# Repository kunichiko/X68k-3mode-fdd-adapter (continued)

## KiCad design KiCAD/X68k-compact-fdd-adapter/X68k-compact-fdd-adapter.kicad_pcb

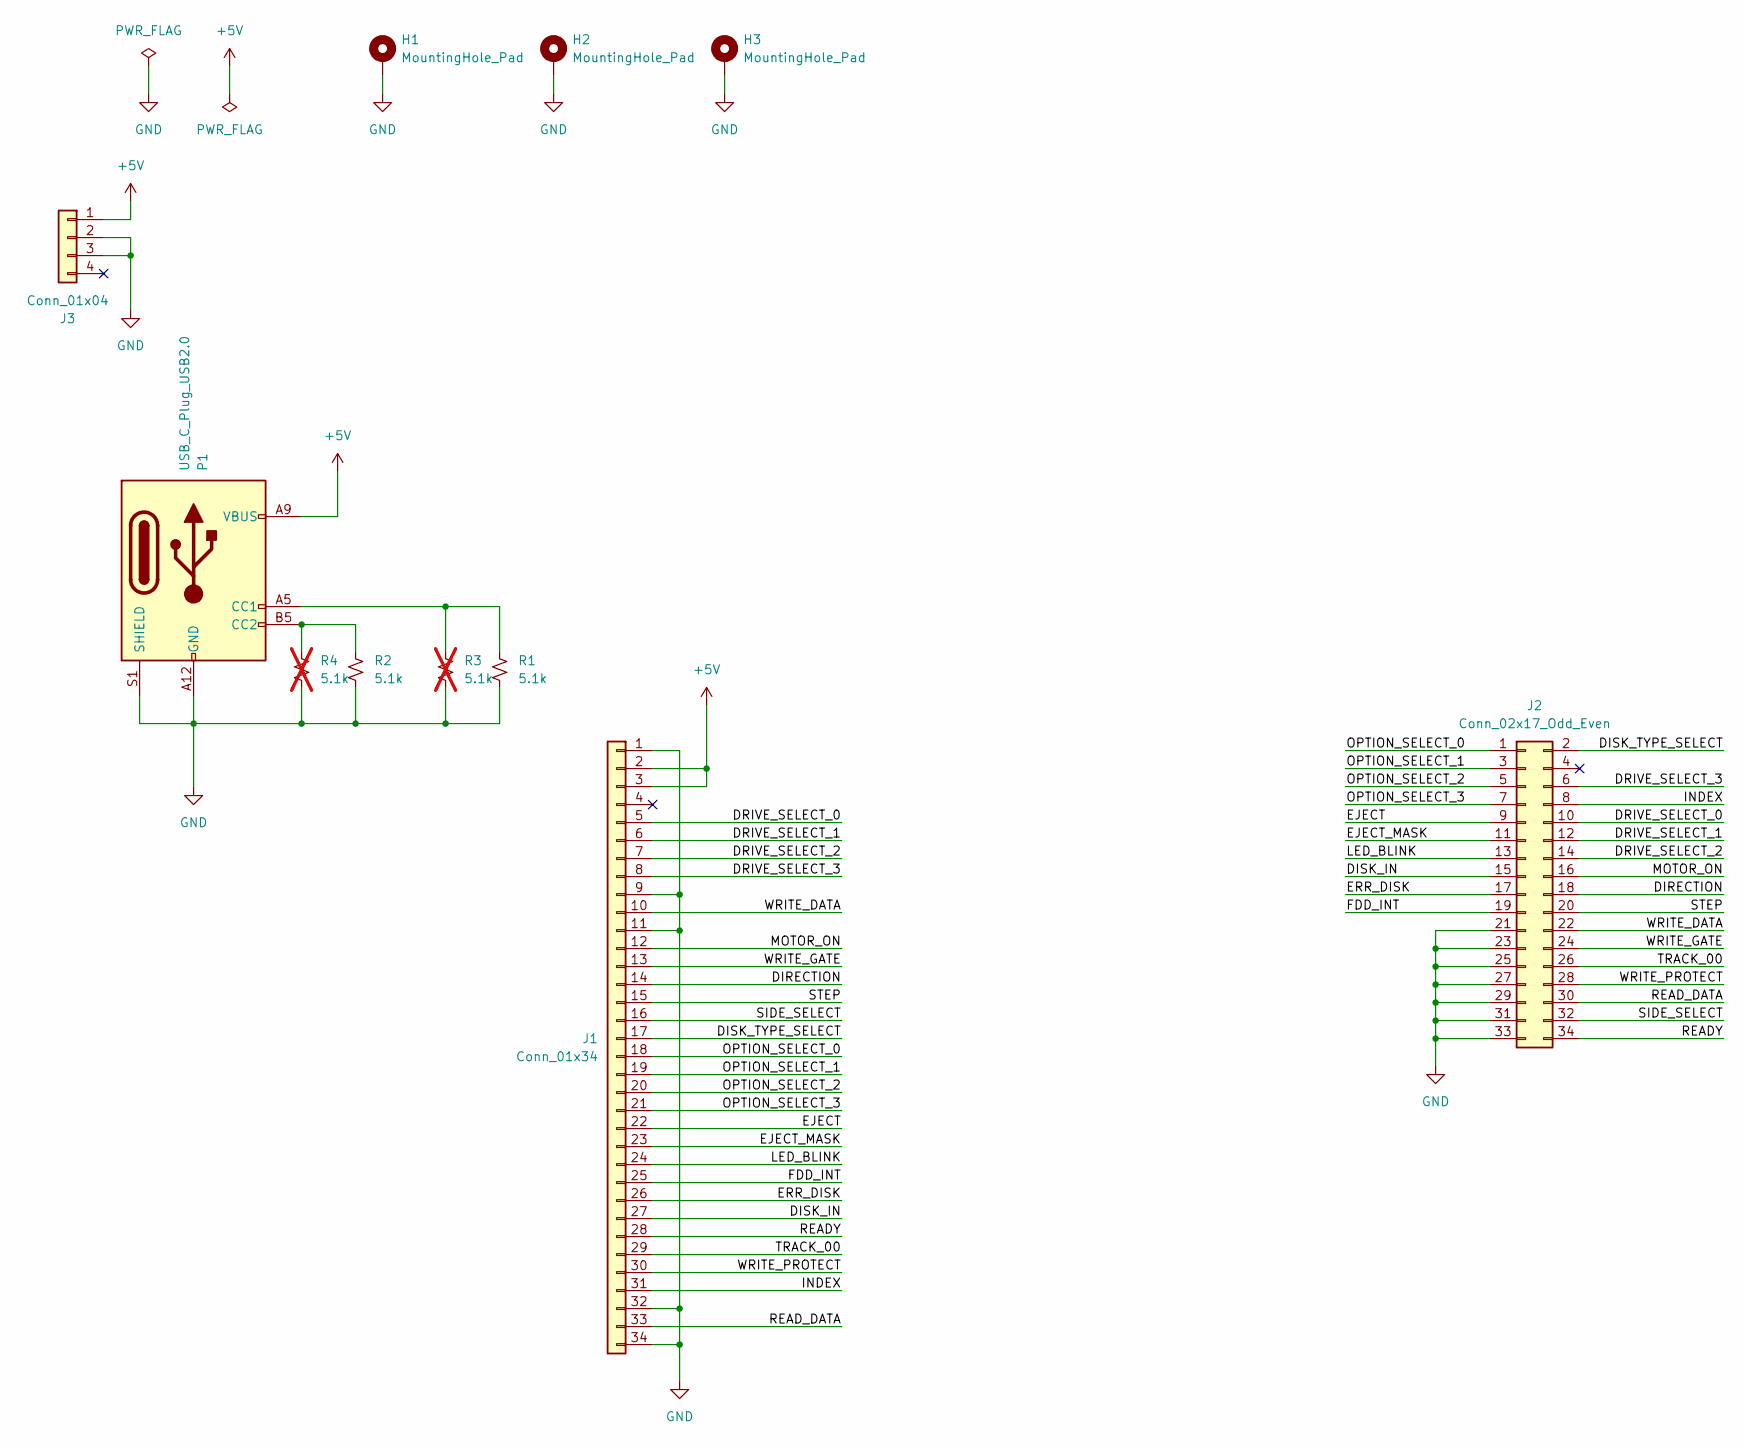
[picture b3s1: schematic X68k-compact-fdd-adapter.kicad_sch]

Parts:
H1, H2, H3: MountingHole_Pad; MountingHole_2.7mm_M2.5_Pad
J1: Conn_01x34; JST-34FE-FCC
J2: Conn_02x17_Odd_Even; PinHeader_2x17_P2.54mm_Horizontal_Mirror; LCSC C725929
J3: Conn_01x04; TE_AMP_171826-4; LCSC C590635
P1: USB_C_Plug_USB2.0; USB_C_Receptacle_GCT_USB4125-xx-x-0190_6P_TopMnt_Horizontal; LCSC C168701
R1, R2: 5.1k; R_0603_1608Metric
R3, R4: 5.1k; R_Axial_DIN0204_L3.6mm_D1.6mm_P5.08mm_Horizontal; not fitted

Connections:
+5V: J1.2, J1.3, J3.1, P1.A9 (VBUS), P1.B9 (VBUS)
/DIRECTION: J1.14, J2.18
/DISK_IN: J1.27, J2.15
/DISK_TYPE_SELECT: J1.17, J2.2
/DRIVE_SELECT_0: J1.5, J2.10
/DRIVE_SELECT_1: J1.6, J2.12
/DRIVE_SELECT_2: J1.7, J2.14
/DRIVE_SELECT_3: J1.8, J2.6
/EJECT: J1.22, J2.9
/EJECT_MASK: J1.23, J2.11
/ERR_DISK: J1.26, J2.17
/FDD_INT: J1.25, J2.19
/INDEX: J1.31, J2.8
/LED_BLINK: J1.24, J2.13
/MOTOR_ON: J1.12, J2.16
/OPTION_SELECT_0: J1.18, J2.1
/OPTION_SELECT_1: J1.19, J2.3
/OPTION_SELECT_2: J1.20, J2.5
/OPTION_SELECT_3: J1.21, J2.7
/READY: J1.28, J2.34
/READ_DATA: J1.33, J2.30
/SIDE_SELECT: J1.16, J2.32
/STEP: J1.15, J2.20
/TRACK_00: J1.29, J2.26
/WRITE_DATA: J1.10, J2.22
/WRITE_GATE: J1.13, J2.24
/WRITE_PROTECT: J1.30, J2.28
GND: H1.1, H2.1, H3.1, J1.1, J1.9, J1.11, J1.32, J1.34, J2.21, J2.23, J2.25, J2.27, J2.29, J2.31, J2.33, J3.2, J3.3, P1.A12 (GND), P1.B12 (GND), P1.S1 (SHIELD), R1.1, R2.2, R3.1, R4.1
unnamed: P1.A5 (CC1), R1.2, R3.2
unnamed: P1.B5 (CC2), R2.1, R4.2

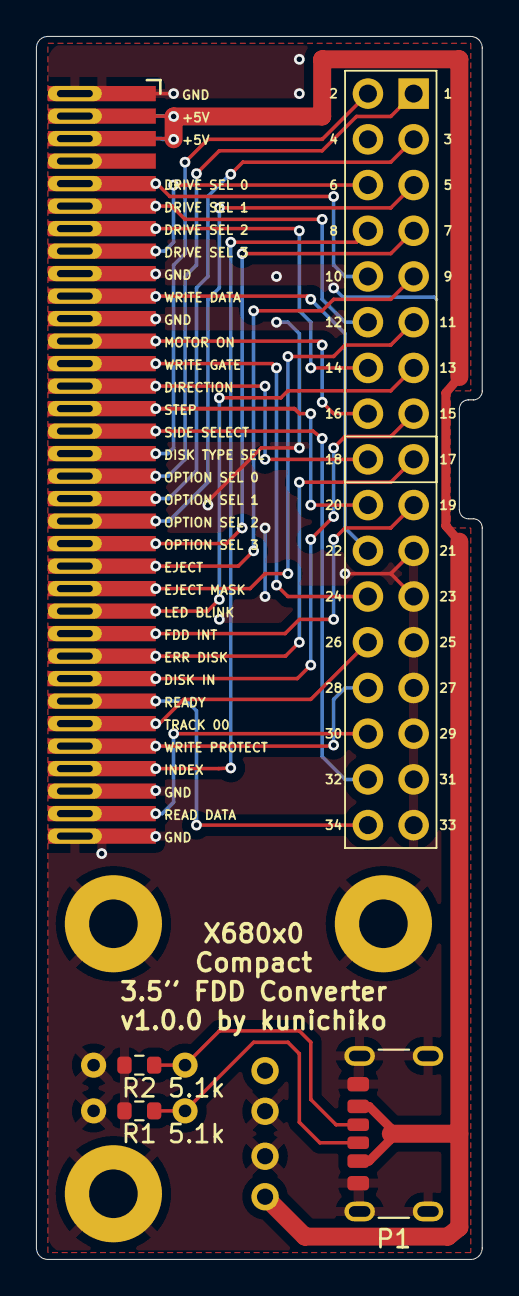
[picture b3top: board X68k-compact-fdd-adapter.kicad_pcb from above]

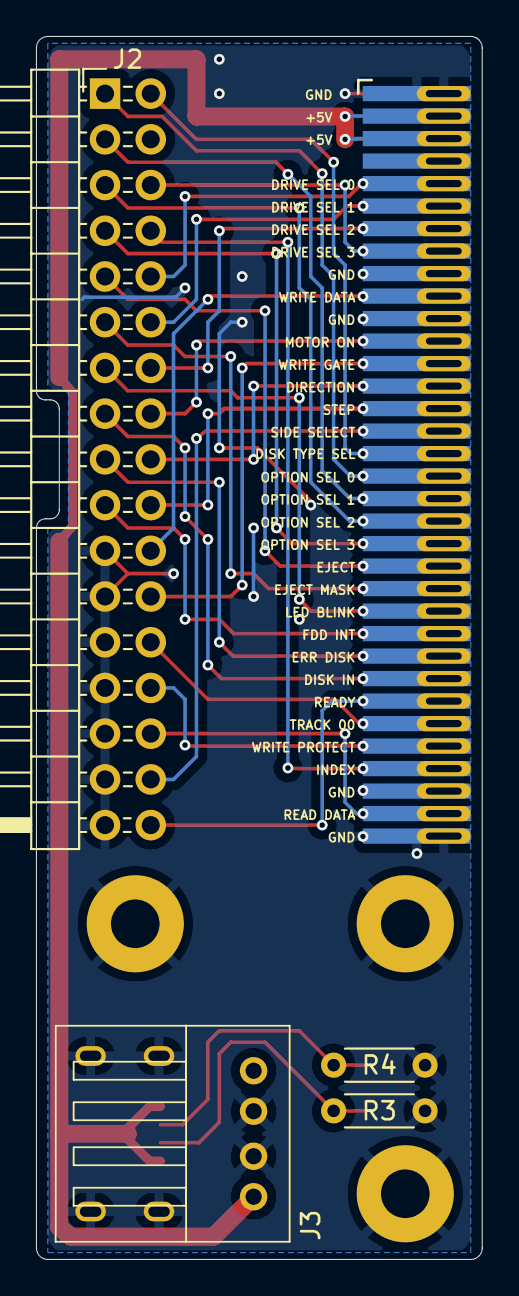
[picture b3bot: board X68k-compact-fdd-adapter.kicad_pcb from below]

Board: 2 copper layers, 24.8 x 67.9 mm, 11 parts (4 on the bottom side), 30 nets.

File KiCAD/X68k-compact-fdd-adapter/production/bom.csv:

Designator,Footprint,Quantity,Value,LCSC Part #
J1,JST-34FE-FFC,1,Conn_01x34,
J2,PinHeader_2x17_P2.54mm_Horizontal_Mirror,1,Conn_02x17_Odd_Even,C725929
J3,TE_AMP_171826-4,1,Conn_01x04,C590635
P1,USB_C_Receptacle_GCT_USB4125-xx-x-0190_6P_TopMnt_Horizontal,1,USB_C_Plug_USB2.0,C168701
"R1, R2",0603,2,5.1k,

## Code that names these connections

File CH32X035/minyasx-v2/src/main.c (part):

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    RCC->APB1PCENR |= RCC_TIM2EN | RCC_TIM3EN;
    RCC->APB2PCENR = RCC_IOPDEN | RCC_IOPCEN | RCC_IOPBEN | RCC_IOPAEN | RCC_TIM1EN | RCC_SPI1EN | RCC_AFIOEN;

    // SPIをデフォルトのPA6,7(MISO,MOSI)から、PC6,7(MISO_3,MOSI_3)に変更するために、Remap Register 1 でリマップする
    AFIO->PCFR1 &= ~(AFIO_PCFR1_SPI1_REMAP);                           // SPI1 remap をクリア
    AFIO->PCFR1 |= AFIO_PCFR1_SPI1_REMAP_1 | AFIO_PCFR1_SPI1_REMAP_0;  // SPI1 remap を 3 (0b11) にセット

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    RCC->APB1PRSTR &= ~RCC_APB1Periph_TIM3;

    // GPIOA
    // PA0 : DRIVE_SELECT_A (入力: Low=inactive, High=active, Pull-Up)
    // PA1 : DRIVE_SELECT_B (入力: Low=inactive, High=active, Pull-Up)
    // PA2 : OPTION_SELECT_A (入力: Low=inactive, High=active, Pull-Up)
    // PA3 : OPTION_SELECT_B (入力: Low=inactive, High=active, Pull-Up)
    // PA4 : OPTION_SELECT_B_PAIR (入力: Low=inactive, High=active, Pull-Up)
    // PA5 : DISK_TYPE_SELECT (入力: Pull-Up, 未使用)
    // PA6 : INDEX_DOSV (入力: INDEX信号, Pull-Up)
    // PA7 : Buzzer (出力: PWM)
    // PA8 : WRITE_GATE_MCU (出力: 将来拡張用)
    // PA9 : WRITE_DATA_MCU (出力: 将来拡張用)
    // PA10: I2C_SCL (I2Cクロック)
    // PA11: I2C_SDA (I2Cデータ)
    // PA12: MOTOR_ON (入力: Low=ON, High=OFF, Pull-Up)
    // PA13: EJECT_n (入力: Low=イジェクト, Pull-Up)
    // PA14: EJECT_MASK_n (入力: Low=イジェクト禁止, Pull-Up)
    // PA15: LED_BLINK_n (入力: Low=点灯, Pull-Up)
    // PA16: X68_PWR (入力: Low=電源ON要求, Pull-Up)
    // PA17: +12V_EXT_DET (High=外部+12V電源接続, Pull-Up)
    // PA18: +5V_EN (Low=Enable, High=Disable)
    // PA19: +12V_EN (Low=Enable, High=Disable)
    // PA20: +12V_EXT_EN (Low=Enable, High=Disable))
    // PA22: DIPSW_DS0 (入力: Pull-Up)
    // PA23: DIPSW_DS1 (入力: Pull-Up)

    // PA0: DRIVE_SELECT_A input
    GPIOA->CFGLR &= ~(0xf << (4 * 0));
    GPIOA->CFGLR |= (GPIO_Speed_In | GPIO_CNF_IN_PUPD) << (4 * 0);
    GPIOA->BSHR = (1 << 0);  // Pull-Up
    // PA1: DRIVE_SELECT_B input
    GPIOA->CFGLR &= ~(0xf << (4 * 1));
    GPIOA->CFGLR |= (GPIO_Speed_In | GPIO_CNF_IN_PUPD) << (4 * 1);
    GPIOA->BSHR = (1 << 1);  // Pull-Up
    // PA2: OPTION_SELECT_A input
    GPIOA->CFGLR &= ~(0xf << (4 * 2));
    GPIOA->CFGLR |= (GPIO_Speed_In | GPIO_CNF_IN_PUPD) << (4 * 2);
    GPIOA->BSHR = (1 << 2);  // Pull-Up
    // PA3: OPTION_SELECT_B input
    GPIOA->CFGLR &= ~(0xf << (4 * 3));
    GPIOA->CFGLR |= (GPIO_Speed_In | GPIO_CNF_IN_PUPD) << (4 * 3);
    GPIOA->BSHR = (1 << 3);  // Pull-Up
    // PA4: OPTION_SELECT_B_PAIR input
    GPIOA->CFGLR &= ~(0xf << (4 * 4));
    GPIOA->CFGLR |= (GPIO_Speed_In | GPIO_CNF_IN_PUPD) << (4 * 4);
    GPIOA->BSHR = (1 << 4);  // Pull-Up
    // PA5: DISK_TYPE_SELECT input
    GPIOA->CFGLR &= ~(0xf << (4 * 5));
    GPIOA->CFGLR |= (GPIO_Speed_In | GPIO_CNF_IN_PUPD) << (4 * 5);
    GPIOA->BSHR = (1 << 5);  // Pull-Up
    // PA6: INDEX_DOSV input
    GPIOA->CFGLR &= ~(0xf << (4 * 6));
    GPIOA->CFGLR |= (GPIO_Speed_In | GPIO_CNF_IN_PUPD) << (4 * 6);
    GPIOA->BSHR = (1 << 6);  // Pull-Up
    // PA7 : Buzzer output. TIM3_CH2 (PWM出力)
    GPIOA->CFGLR &= ~(0xf << (4 * 7));
    // GPIOA->CFGLR |= (GPIO_Speed_50MHz | GPIO_CNF_OUT_PP_AF) << (4 * 7);
    GPIOA->CFGLR |= (GPIO_Speed_50MHz | GPIO_CNF_OUT_PP) << (4 * 7);
    //  GPIOA->CFGLR |= (GPIO_Speed_In | GPIO_CNF_IN_PUPD) << (4 * 7);
    GPIOA->BCR = (1 << 7);  // Low出力にする
    // GPIOA->BSHR = (1 << 7);  // High出力にする (Buzzer OFF)
    // PA8: WRITE_GATE_MCU output
    GPIOA->CFGHR &= ~(0xf << (4 * (8 - 8)));
    GPIOA->CFGHR |= (GPIO_Speed_50MHz | GPIO_CNF_OUT_PP) << (4 * (8 - 8));
    GPIOA->BCR = (1 << 8);  // 0を出力 (この先にいるFETをOFFにする)
    // PA9: WRITE_DATA_MCU output
    GPIOA->CFGHR &= ~(0xf << (4 * (9 - 8)));
    GPIOA->CFGHR |= (GPIO_Speed_50MHz | GPIO_CNF_OUT_PP) << (4 * (9 - 8));
    GPIOA->BCR = (1 << 9);  // 0を出力 (この先にいるFETをOFFにする)
    // PA10: I2C_SCL
    // PA11: I2C_SDA
    // PA12: MOTOR_ON input
    GPIOA->CFGHR &= ~(0xf << (4 * (12 - 8)));
    GPIOA->CFGHR |= (GPIO_Speed_In | GPIO_CNF_IN_PUPD) << (4 * (12 - 8));
    GPIOA->BSHR = (1 << 12);  // Pull-Up
    // PA13: EJECT_n input
    GPIOA->CFGHR &= ~(0xf << (4 * (13 - 8)));
    GPIOA->CFGHR |= (GPIO_Speed_In | GPIO_CNF_IN_PUPD) << (4 * (13 - 8));
    GPIOA->BSHR = (1 << 13);  // Pull-Up
    // PA14: EJECT_MASK_n input
    GPIOA->CFGHR &= ~(0xf << (4 * (14 - 8)));
    GPIOA->CFGHR |= (GPIO_Speed_In | GPIO_CNF_IN_PUPD) << (4 * (14 - 8));
    GPIOA->BSHR = (1 << 14);  // Pull-Up
    // PA15: LED_BLINK_n input
    GPIOA->CFGHR &= ~(0xf << (4 * (15 - 8)));
    GPIOA->CFGHR |= (GPIO_Speed_In | GPIO_CNF_IN_PUPD) << (4 * (15 - 8));
    GPIOA->BSHR = (1 << 15);  // Pull-Up
    // PA16: X68_PWR input
    GPIOA->CFGXR &= ~(0xf << (4 * (16 - 16)));
    GPIOA->CFGXR |= (GPIO_Speed_In | GPIO_CNF_IN_PUPD) << (4 * (16 - 16));
    GPIOA->BSXR = (1 << (16 - 16));  // Pull-Up
    // PA17: +12V_EXT_DET input
    GPIOA->CFGXR &= ~(0xf << (4 * (17 - 16)));
    GPIOA->CFGXR |= (GPIO_Speed_In | GPIO_CNF_IN_PUPD) << (4 * (17 - 16));
    GPIOA->BSXR = (1 << (17 - 16));  // Pull-Up
    // PA18: +5V_EN output
    GPIOA->CFGXR &= ~(0xf << (4 * (18 - 16)));
    GPIOA->CFGXR |= (GPIO_Speed_50MHz | GPIO_CNF_OUT_PP) << (4 * (18 - 16));
    GPIOA->BCR = (1 << (18));  // Disable (+5V_EN=Low)
    // GPIOA->BSXR = (1 << (18 - 16)); // Enable (+5V_EN=High)
    // PA19: +12V_EN output
    GPIOA->CFGXR &= ~(0xf << (4 * (19 - 16)));
    GPIOA->CFGXR |= (GPIO_Speed_50MHz | GPIO_CNF_OUT_PP) << (4 * (19 - 16));
    GPIOA->BCR = (1 << (19));  // Disable (+12V_EN=Low)
    // GPIOA->BSXR = (1 << (19 - 16)); // Enable (+12V_EN=High)
    //  PA20: +12V_EXT_EN output
    GPIOA->CFGXR &= ~(0xf << (4 * (20 - 16)));
    GPIOA->CFGXR |= (GPIO_Speed_50MHz | GPIO_CNF_OUT_PP) << (4 * (20 - 16));
    GPIOA->BCR = (1 << (20));  // Disable (+12V_EXT_EN=Low)
    // GPIOA->BSXR = (1 << (20 - 16)); // Enable (+12V_EXT_EN=High)

    // PA22: DIPSW_DS0 input
    GPIOA->CFGXR &= ~(0xf << (4 * (22 - 16)));
    GPIOA->CFGXR |= (GPIO_Speed_In | GPIO_CNF_IN_PUPD) << (4 * (22 - 16));
    GPIOA->BSXR = (1 << (22 - 16));  // Pull-Up
    // PA23: DIPSW_DS1 input
    GPIOA->CFGXR &= ~(0xf << (4 * (23 - 16)));
    GPIOA->CFGXR |= (GPIO_Speed_In | GPIO_CNF_IN_PUPD) << (4 * (23 - 16));
    GPIOA->BSXR = (1 << (23 - 16));  // Pull-Up

    // GPIOB
    // PB0 : MODE_SELECT_GP (入力: Low=360RPM, High=300RPM, 逆のものもあるらしい)
    // PB1 : IN_USE_MCU (出力: Low=アクティブ, High=非アクティブ)
    // PB2 : DRIVE_SEL_DOSV_A (未使用, High-Z)
    // PB3 : DRIVE_SEL_DOSV_B (未使用, High-Z)
    // PB4 : DISK_CHANGE_DOSV (入力: Low=ディスクチェンジ, Pull-Up)
    // PB5 : (未使用)
    // PB6 : LOCK_REQ (出力: Low=要求, High=非要求)
    // PB7 : LOCK_ACK (入力: High=アクティブ, Pull-Down)
    // PB8 : WRITE_GATE_GP (入力: フロッピーディスクの書き込み許可信号)
    // PB9 : READ_DATA_DOSV (入力: フロッピーディスクの読み出しデータ)
    // PB10: WRITE_DATA_GP (入力: フロッピーディスクの書き込みデータ)
    // PB11: TRACK0_DOSV (入力: Low=トラック0, Pull-Up)
    // PB12: READY_MCU_A (出力: Low=準備完了, High=準備完了でない)
    // PB13: READY_MCU_B (出力: Low=準備完了

    // PB0: MODE_SELECT_GP input
    GPIOB->CFGLR &= ~(0xf << (4 * 0));
    GPIOB->CFGLR |= (GPIO_Speed_In | GPIO_CNF_IN_FLOATING) << (4 * 0);
    // PB1: IN_USE_MCU output
    GPIOB->CFGLR &= ~(0xf << (4 * 1));
    GPIOB->CFGLR |= (GPIO_Speed_50MHz | GPIO_CNF_OUT_PP) << (4 * 1);
    GPIOB->BCR = (1 << 1);
    // PB2: DRIVE_SELECT_DOSV_A output (未使用)
    GPIOB->CFGLR &= ~(0xf << (4 * 2));
    GPIOB->CFGLR |= (GPIO_Speed_In | GPIO_CNF_IN_FLOATING) << (4 * 2);
    // PB3: DRIVE_SELECT_DOSV_B output (未使用)
    GPIOB->CFGLR &= ~(0xf << (4 * 3));
    GPIOB->CFGLR |= (GPIO_Speed_In | GPIO_CNF_IN_FLOATING) << (4 * 3);
    // PB4: DISK_CHANGE_DOSV input
    GPIOB->CFGLR &= ~(0xf << (4 * 4));
    GPIOB->CFGLR |= (GPIO_Speed_In | GPIO_CNF_IN_PUPD) << (4 * 4);
    GPIOB->BCR = (1 << 4);
    // PB5: (未使用)
    GPIOB->CFGLR &= ~(0xf << (4 * 5));
    GPIOB->CFGLR |= (GPIO_Speed_In | GPIO_CNF_IN_FLOATING) << (4 * 5);
    // PB6: LOCK_REQ output
    GPIOB->CFGLR &= ~(0xf << (4 * 6));
    GPIOB->CFGLR |= (GPIO_Speed_50MHz | GPIO_CNF_OUT_PP) << (4 * 6);
    GPIOB->BCR = (0 << 6);
    // PB7: LOCK_ACK input
    GPIOB->CFGLR &= ~(0xf << (4 * 7));
    GPIOB->CFGLR |= (GPIO_Speed_In | GPIO_CNF_IN_PUPD) << (4 * 7);
    GPIOB->BCR = (1 << 7);  // Pull-Up
    // PB8: WRITE_GATE_GP input
    GPIOB->CFGHR &= ~(0xf << (4 * (8 - 8)));
    GPIOB->CFGHR |= (GPIO_Speed_In | GPIO_CNF_IN_FLOATING) << (4 * (8 - 8));
    // GPIOB->BSHR = (1 << 8);
    //  PB9: READ_DATA_DOSV input
    GPIOB->CFGHR &= ~(0xf << (4 * (9 - 8)));
    GPIOB->CFGHR |= (GPIO_Speed_In | GPIO_CNF_IN_PUPD) << (4 * (9 - 8));
    GPIOB->BSHR = (1 << 9);  // Pull-Up
    // PB10: WRITE_DATA_DOSV input
    GPIOB->CFGHR &= ~(0xf << (4 * (10 - 8)));
    GPIOB->CFGHR |= (GPIO_Speed_In | GPIO_CNF_IN_FLOATING) << (4 * (10 - 8));
    // GPIOB->BSHR = (1 << 10);  // Pull-Up
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    GPIOB->CFGHR &= ~(0xf << (4 * (11 - 8)));
    GPIOB->CFGHR |= (GPIO_Speed_In | GPIO_CNF_IN_PUPD) << (4 * (11 - 8));
    GPIOB->BSHR = (1 << 11);  // Pull-Up
    // PB12: READY_MCU_A output
    GPIOB->CFGHR &= ~(0xf << (4 * (12 - 8)));
    GPIOB->CFGHR |= (GPIO_Speed_50MHz | GPIO_CNF_OUT_PP) << (4 * (12 - 8));
    GPIOB->BSHR = (1 << 12);
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
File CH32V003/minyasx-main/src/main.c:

#include "main.h"

#include <stdarg.h>
#include <stdio.h>

#include "ch32v003_GPIO_branchless.h"
#include "ch32v003fun.h"

#include <ssd1306_txt.h>        // OLED text functions

#include "port_polling.h"

#define WS2812BSIMPLE_IMPLEMENTATION
#include "ws2812b_simple.h"

#define MAIN_LOOP_INTERVAL 100  // 100msごとにメインループを回す

void update_fdd_led();

/**
 * @brief 設定ピンによって、MODE_SELECTの論理を反転するかどうかのフラグ
 *
 */
bool mode_select_invert = 0;

int main() {
    SystemInit();

    Delay_Ms(100);
  
    // Setup OLED
    OLED_init();
    OLED_clear();
    OLED_printf("Minyax-X");

    debugprint("UP\n");

    // 使用するペリフェラルを有効にする
    // IOPDEN = Port D clock enable
    // IOPCEN = Port C clock enable
    // IOPAEN = Port A clock enable
    // TIM1 = Timer 1 module clock enable
    // AFIO = Alternate Function I/O module clock enable
    RCC->APB2PCENR = RCC_IOPDEN | RCC_IOPCEN | RCC_IOPAEN | RCC_TIM1EN | RCC_AFIOEN;

    // リセットレジスタのTIM1RSTをセットしてからクリアすると、
    // タイマー1がリセットされる
    RCC->APB2PRSTR = RCC_TIM1RST;
    RCC->APB2PRSTR = 0;

    //
    // GPIOの設定
    //

    // GPIO A
    // A1: READY,                   Output, Push-Pull
    // A2: BUZZER,                  Output, Push-Pull
    GPIOA->CFGLR &= ~(0xf << (4 * 1));
    GPIOA->CFGLR |= (GPIO_Speed_50MHz | GPIO_CNF_OUT_PP) << (4 * 1);
    GPIOA->CFGLR &= ~(0xf << (4 * 2));
    GPIOA->CFGLR |= (GPIO_Speed_50MHz | GPIO_CNF_OUT_PP) << (4 * 2);

    // GPIO C
    // C0: LED_DATA, Output, push-pull
    //     C0にはスイッチがついていて起動時にHighかLowかでMODE_SELECTの論理を決める
    // C1: I2C SDA
    // C2: I2C SCL
    // C3: FDD INDEX,               Input, pull-up
    // C4: FDD MOTOR_ON,            Input, pull-up
    // C5: FDD DRIVE_SELECT,        Input, pull-up
    // C6: FDD OPTION_SELECT_PAIR,  Input, pull-up
    // C7: FDD OPTION_SELECT,       Input, pull-up

    GPIOC->CFGLR &= ~(0xf << (4 * 0));
    GPIOC->CFGLR |= (GPIO_Speed_In | GPIO_CNF_IN_PUPD) << (4 * 0);
    GPIOC->BSHR = GPIO_Pin_0;  // プルアップを有効にする
    if ((GPIOC->INDR & GPIO_Pin_0) == 0) {
        mode_select_invert = 1;
    } else {
        mode_select_invert = 0;
    }
    debugprint("MODE_SELECT_INVERT: %d\n", mode_select_invert);

    // C0を出力にする
    GPIOC->CFGLR &= ~(0xf << (4 * 0));
    GPIOC->CFGLR |= (GPIO_Speed_50MHz | GPIO_CNF_OUT_PP) << (4 * 0);

    GPIOC->CFGLR &= ~(0xf << (4 * 3));
    GPIOC->CFGLR |= (GPIO_Speed_In | GPIO_CNF_IN_PUPD) << (4 * 3);
    GPIOC->CFGLR &= ~(0xf << (4 * 4));
    GPIOC->CFGLR |= (GPIO_Speed_In | GPIO_CNF_IN_PUPD) << (4 * 4);
    GPIOC->CFGLR &= ~(0xf << (4 * 5));
    GPIOC->CFGLR |= (GPIO_Speed_In | GPIO_CNF_IN_PUPD) << (4 * 5);
    GPIOC->CFGLR &= ~(0xf << (4 * 6));
    GPIOC->CFGLR |= (GPIO_Speed_In | GPIO_CNF_IN_PUPD) << (4 * 6);
    GPIOC->CFGLR &= ~(0xf << (4 * 7));
    GPIOC->CFGLR |= (GPIO_Speed_In | GPIO_CNF_IN_PUPD) << (4 * 7);

    // PUPDモードの入力ピンに1を出力すると、プルアップになる
    // C3-C7をプルアップにする
    GPIOC->BSHR = GPIO_Pin_3 | GPIO_Pin_4 | GPIO_Pin_5 | GPIO_Pin_6 | GPIO_Pin_7;

    // GPIO D
    // D0: DISK_IN_GEN,         Output, push-pull
    // D1: DISK_CHANGE_DOSV,    Input, pull-up
    // D2: DRIVE_SELECT_DOSV_1, Output, Open-drain
    // D3: MODE_SELECT_DOSV,    Output, Open-drain
    // D4: EJECT_MASK,          Input, pull-up
    // D5: EJECT,               Input, pull-up
    // D6: LED_BLINK,           Input, pull-up
    // D7: FDD_INT_GEN,         Output, push-pull
    GPIOD->CFGLR &= ~(0xf << (4 * 0));
    GPIOD->CFGLR |= (GPIO_Speed_50MHz | GPIO_CNF_OUT_PP) << (4 * 0);
    GPIOD->CFGLR &= ~(0xf << (4 * 1));
    GPIOD->CFGLR |= (GPIO_Speed_In | GPIO_CNF_IN_PUPD) << (4 * 1);
    GPIOD->CFGLR &= ~(0xf << (4 * 2));
    GPIOD->CFGLR |= (GPIO_Speed_50MHz | GPIO_CNF_OUT_OD) << (4 * 2);
    GPIOD->CFGLR &= ~(0xf << (4 * 3));
    GPIOD->CFGLR |= (GPIO_Speed_50MHz | GPIO_CNF_OUT_OD) << (4 * 3);
    GPIOD->CFGLR &= ~(0xf << (4 * 4));
    GPIOD->CFGLR |= (GPIO_Speed_In | GPIO_CNF_IN_PUPD) << (4 * 4);
    GPIOD->CFGLR &= ~(0xf << (4 * 5));
    GPIOD->CFGLR |= (GPIO_Speed_In | GPIO_CNF_IN_PUPD) << (4 * 5);
    GPIOD->CFGLR &= ~(0xf << (4 * 6));
    GPIOD->CFGLR |= (GPIO_Speed_In | GPIO_CNF_IN_PUPD) << (4 * 6);
    GPIOD->CFGLR &= ~(0xf << (4 * 7));
    GPIOD->CFGLR |= (GPIO_Speed_50MHz | GPIO_CNF_OUT_PP) << (4 * 7);

    // PUPDモードの入力ピンに1を出力すると、プルアップになる
    // D1, D4, D5, D6をプルアップにする
    GPIOD->BSHR = GPIO_Pin_1 | GPIO_Pin_4 | GPIO_Pin_5 | GPIO_Pin_6;

    // MODE_SELECTの論理の初期設定
    // 初期状態はX68000の標準フォーマット(360RPM, 1.2MB)とする
    if (mode_select_invert) {
        // 反転時はMODE_SELECT_DOSV(D3)をアクティブ(Low)にすると1.2MB
        GPIOD->BCR = GPIO_Pin_3;
    } else {
        // 通常時はMODE_SELECT_DOSV(D3)をインアクティブ(High)にすると1.2MB
        GPIOD->BSHR = GPIO_Pin_3;
    }

    // Timer 1 を 10us で割り込みを発生させる
    // 10us = 100kHz で割り込みを発生させる

    port_polling_init();

    while (1) {
        Delay_Ms(MAIN_LOOP_INTERVAL);
        update_fdd_led();
    }
}

/*
 X68000の純正ドライブのLEDの仕様は以下の通り

* アクセスランプ
    * メディア挿入時
        * アクセスなし            緑点灯
        * アクセスあり            赤点灯
    * メディア未挿入時
        * LED_BLINK = false     消灯
        * LED_BLINK = true      緑点滅
* イジェクトランプ
    * メディア挿入時
        * EJECT_MASK = false     緑点灯 (マスクがfalseなので、イジェクト可能)
        * EJECT_MASK = true      消灯   (マスクがtrueなので、イジェクト不可)
    * メディア未挿入時
        * 常時                   消灯

 ※メディアの挿入/未挿入の判断、アクセスの有無はドライブ自体が行なっている。

 上記を踏まえ、本装置では以下のように実装する。

* メディア挿入/未挿入の判断
    * READY信号がアクティブになったら挿入状態に移行
    * DISK_CHANGEがアクティブになったら未挿入状態に移行
* アクセスあり/なしの判断
    * DRIVE_SELECTがアクティブになっている間はアクセスあり
* LED_BLINK
    * DRIVE_SELECTアサート時の値を保持
* EJECT_MASK
    * DRIVE_SELECTアサート時の値を保持
 */

volatile bool in_access = 0;
volatile bool media_inserted = 0;
volatile bool led_blink = 0;
volatile bool eject = 0;
volatile bool eject_mask = 0;

int led_blink_counter = 0;

// ACCESS [G,R,B]
// EJECT  [G,R,B]
uint8_t led_data[3 * 2] = {0, 0, 0, 0, 0, 0};
#define ACCESS_G 0
#define ACCESS_R 1
#define ACCESS_B 2
#define EJECT_G 3
#define EJECT_R 4
#define EJECT_B 5
#define LED_BLINK_INTERVAL 1000 * 2
#define LED_BRIGTHNESS 10

void update_fdd_led() {
    // 一旦データをクリア
    for (int i = 0; i < 3; i++) {
        led_data[i] = 0;
        led_data[i + 3] = 0;
    }
    // LED_BLINK カウンターの更新
    led_blink_counter += MAIN_LOOP_INTERVAL;
    if (led_blink_counter >= LED_BLINK_INTERVAL) {
        led_blink_counter = 0;
    }
    int led_blink_brightness = led_blink_counter < LED_BLINK_INTERVAL / 2 ? LED_BRIGTHNESS : 0;

    // アクセスランプの判断
    if (media_inserted) {
        // メディア挿入
        if (in_access) {
            // アクセスあり = 赤点灯
            led_data[ACCESS_R] = LED_BRIGTHNESS;
        } else {
            // アクセスなし = 緑点灯
            led_data[ACCESS_G] = LED_BRIGTHNESS;
        }
    } else {
        // メディア未挿入の場合は LED_BLINK によって点滅か点灯
        if (led_blink) {
            led_data[ACCESS_G] = led_blink_brightness;
        } else {
            led_data[ACCESS_G] = 0;
        }
    }
    // イジェクトランプの判断
    if (media_inserted) {
        // メディア挿入
        if (eject_mask) {
            // イジェクト不可 = 消灯
            led_data[EJECT_G] = 0;
        } else {
            // イジェクト可能 = 緑点灯
            if (revolution_2hd_144) {
                led_data[EJECT_B] = LED_BRIGTHNESS;  // 1.44MBの場合は青点灯
            } else {
                led_data[EJECT_G] = LED_BRIGTHNESS;
            }
        }
    } else {
        // メディア未挿入の場合は消灯
        led_data[EJECT_G] = 0;
    }

    // PD1 (SWIOとの共用ピン) が読めるかどうかのテスト
    // if(GPIOD->INDR & GPIO_Pin_1) {
    //     led_data[EJECT_B] = LED_BRIGTHNESS;
    // } else {
    //     led_data[EJECT_R] = 0;
    // }

    // 更新
    WS2812BSimpleSend(GPIOC, 0, led_data, 6);
}

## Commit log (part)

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2025-01-08 一通り配線した(未チェック)
2025-01-08 一通りの配線、調整を入れたバージョン
2025-01-08 基板形状を見直した
2025-01-08 v1.0.0注文版
2025-01-08 LCIC→LCSCに修正
2025-01-11 FDD側の2x17ピンソケット(フィメールヘッダ)のLCSC型番が判明したので入力した
2025-01-14 BuzzerシンボルをSpeakerシンボルに変更
2025-01-22 マイコンのコードを書き始めた
2025-01-22 現状をコミット(特に修正はしていないはずだが……)
2025-01-22 .gitignoreを追加
2025-01-23 コードを整理
2025-01-26 9scsetの自動回転数制御を使って、9scfmtの標準(1.2M)とIBM(1.44M)のフォーマットを作り分けられるようになった
2025-01-26 EJECT, EJECT_MASK, LED_BLINKのオプション信号を拾うようにした
2025-04-13 ライブラリパスが絶対パスになっていたので、プロジェクトフォルダからの相対パスになるように修正
2025-04-13 X680x0 Compactの 3.5インチドライブを34ピンフラットケーブルに変換する基板を作成
2025-05-10 プロジェクトを整理
2025-07-28 KiCAD9に更新
2025-08-24 OLEDに文字を出せるようにした
2025-08-31 Minyas-XのV2基板の回路図を一通り日いいたので一旦コミット
2025-08-31 サブモジュールの変更に追従
2025-08-31 DRCエラー修正
2025-08-31 アノテーション再実施
2025-08-31 フットプリントを一通り割り当てた
2025-09-02 PCBの配線完了
2025-09-03 基板の外径を変更して、底面部のネジ穴に合うホールを追加
2025-09-03 部品の配置、シルクを調整
2025-09-03 シルクをさらに調整
2025-09-03 試作基板の発注
2025-09-07 JLCPCB試作版のアーカイブ
2025-09-07 フロントパネルを作り始めた
2025-09-10 フロントパネル-形状確認の途中
2025-09-12 v2.0.1向けの修正を一通り入れたので一旦コミット
2025-09-14 V2基板のCH32X035用のコードを書き始めた(Lチカまで)
2025-09-14 電源連動のためにプリンタ端子に繋ぐ基板をつくりはじめた
2025-09-14 外部連動端子の回路のデジトラをFETに変更した
2025-09-14 SPIをDMAで動かしてLED制御できるようになった
2025-09-14 リファクタリングしてフォルダに整理した
2025-09-14 OLEDもハードウェアI2Cで制御できるようになった
2025-09-14 GreenPAKの書き込みができるようになってきたので一旦コミット。 Intel Hexファイルから自動的に Cのデータ文を生成。
2025-09-14 複数のGreenPAKのかきかえ、ダンプに対応
2025-09-14 電圧、電流を読めるようにした
2025-09-15 PDのネゴシエーションコードを書いていたが、わけわからなくなってきたので一旦仕切り直しするため、現状をコミット
2025-09-15 別のPD対応コードを移植したら動いた
2025-09-16 電源周りの回路を修正
2025-09-16 現状をコミット
2025-09-16 フォーマッターを変更
2025-09-16 PDから+12Vが取れなかった場合は、 INA3221で電圧を計測して、VBUSが+5Vであることを念の為調べた上で +5Vラインを有効にするようにした
2025-09-17 タイマーでインデックスの周期を測れるようにした
2025-09-17 * DCDCの出力の直後のダイオードをFETに変更 * DriveSelectのAとBが逆に配線されていた問題を修正
2025-09-19 READ_DATAをタイマーでキャプチャしておよそのビットレートを推測できるようにした
2025-09-19 - GreenPAKの Drive Selectと Option Selectのロジックが間違っていたので修正 - Drive Selectをポーリングするようにしてみた
2025-09-19 bps計測の負荷を少し下げた
2025-09-19 68側のFDDの信号に割り込みで反応するようにしてみた
2025-09-20 2ドライブ同時に動かしてファイルコピーまで動いたところ
2025-09-20 * 9SCDRVの自動3モード切り替えができるようになった * OPTION_SELECTの配線が一つ増えたので回路も変更 (OPTION_SELECT_B_PAIR) * 2つのドライブで、1つは 1.2M、もう1つは1.44MBという状態でコピーに成功
2025-09-23 * フロントパネルのキー操作ができるようにした * 画面のページ切り替えができるようにした * FDDの回転数とbpsの推定コードを修正した
2025-09-23 メニューの仮実装
2025-09-23 USB-PD のステータス表示画面を作成
2025-09-23 UI実装を整理して、デバッグ出力を別ページに追い出したりした
2025-09-23 デバッグページをさらに2つにわけた
2025-09-24 UIフレームワークをリファクタリングして、選択メニューを実装できるようにした
2025-09-24 メニューのリファクタリング common設定画面からMOTOR_ONできるようにしてみた
2025-09-24 FDD設定画面の実装
2025-09-25 Ejectボタンの動作確認
2025-09-25 Buzzerで音が鳴らせるようにした GP3の更新は、68電源連動のための布石で、INDEX端子の電圧を監視できるようにするための準備
2025-09-26 * WCH-LinkEを接続できるようにピン配置を変更 * GP_ENABLEをPC6へ * CONTROLLER_OPTIONを廃止 * Warningを除去 * X68000の電源ONを検出するためにINDEX信号をGP経由で監視できるようにした(GPに専用端子を追加) *
2025-09-26 メディアの論理イジェクトができるようにコードと回路を少し修正した(未確認)
2025-09-26 イジェクトボタンが効くようになった
2025-09-26 X68000側からのEJECT信号に対応
2025-09-27 リセット時にUSB-PDの再ネゴシエーションができなかった問題を修正 スクロール可能なページを作り、動作ログをそちらに表示するようにした
2025-09-27 ドライブの接続状態の管理をもう少しまともにした
2025-09-27 まだ完全ではないが、ドライブの状態とメディアの検出状態の管理をリファクタリングしたので一旦コミット
2025-09-27 メディア検出が割と動くようになってきたので一旦コミット
2025-09-27 シーク用のSTEP信号を取りこぼすことがあったので、STEP信号はマイコンを経由せずに直結できるように修正した この構成で、かなり安定して動くようになった
2025-09-28 ログ出力メソッドの追加 ID3にセットした場合にドライブBを無効化する処理の追加 デバッガ接続用の設定を追加 その他コードの整理
2025-09-28 基板上のGreenPAKをひとつ増やせるように、フロントパネルのGreenPAKの番号をGP4→GP5に変更した ui_log() のバグを修正した
2025-09-28 DriveSelectをマイコンを経由せずに直結する仕組みを入れるテスト用のコード(暫定)
2025-09-30 V2.1.0の基板を引き切った
2025-09-30 サブモジュール更新
2025-09-30 DIRECTIONをマイコンを経由しないようにする実験(うまくいった)
2025-09-30 フロントパネル周りの配線を見直した
2025-10-01 PCBA発注のために部品番号などを追加した
2025-10-01 v2.1.0のPCBA発注
2025-10-01 一部部品が未実装になっていたりしたので修正して出しなおした
2025-10-02 JLCPCB製造版 v2.1.2
2025-10-02 v2.0.1基板にパッチを当てて動作確認用(まだ途中)
2025-10-02 v2.0.1の基板に当てたパッチを回路図に反映
2025-10-02 LOCK_ACKのパッチ
2025-10-02 LOCK_REQ/LOCK_ACKの実装をして、SEEKできるところまで確認
2025-10-03 基板構成変更後、SEEKができるようになったので一旦コミット
2025-10-04 2ドライブ間コピーが安定して動くバージョン 9scdrvの300RPM対応が動かなくなっていた問題も修正
2025-10-04 - INDEX端子によるX68000の電源連動の仕組みを少し修正 - MODE_SELECTの極性反転の実装 - RPM計測が動かなくなっていた問題を修正
2025-10-04 設定をフラッシュに保存できるようにした
2025-10-06 * メディア挿抜検出のチューニング * BOOT画面の実装の調整 * BOOT画面でスリープ状態からボタンダブルクリックで強制ONできるように * その他タイミング調整
2025-10-11 IN_USE信号生成機能の対応 GreenPAK 5 (コントローラー) の書き込みができい問題を修正 MI68-2025ロゴ対応
2025-10-16 68の電源ON検出にINDEXだけでなくREAD_DATAのプルアップも見るようにして検出率を上げた
2025-10-16 * EJECT信号を誤検知することがある問題に簡易的な対処を入れた * MEDIA WAITNG状態が一瞬で終わってしまうことがある問題を修正 * MEDIA WAITING状態の表示を他の状態と区別して表示できるようにした
2025-10-18 シンボルを微調整
2025-10-24 LEDのブリンクテストを追加
2025-10-24 低電圧検出の閾値を調整
2025-10-24 OPTION関連信号のラッチ方法をDMAを使う方法に修正中（途中）
2025-11-03 細かい基板のパッチを当てた * MODE_SELECT をGPからドライブできるように配線した * FDD電源出力コネクタを少し外に出した * GP1、GP5のI2Cを切り離せるようにした * GP5のI2C を5V系に変更 * WCH-LinkE の接続コネクタが鏡像になっていた問題を修正
2025-11-03 v2.1.3 基板で起動するように修正
2025-11-03 v2.1.3基板で「ディスクが入っていません」になる問題を修正
2025-11-04 * V2.1.2基板で MODE_SELECTが正常に機能するようになった * RPM制御をNONE(ドライブのデフォルト回転数)にしている時に、OLEDの表示が"S:---" になるようにした
